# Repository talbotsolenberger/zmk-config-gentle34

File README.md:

This is a shield module for use with ZMK.

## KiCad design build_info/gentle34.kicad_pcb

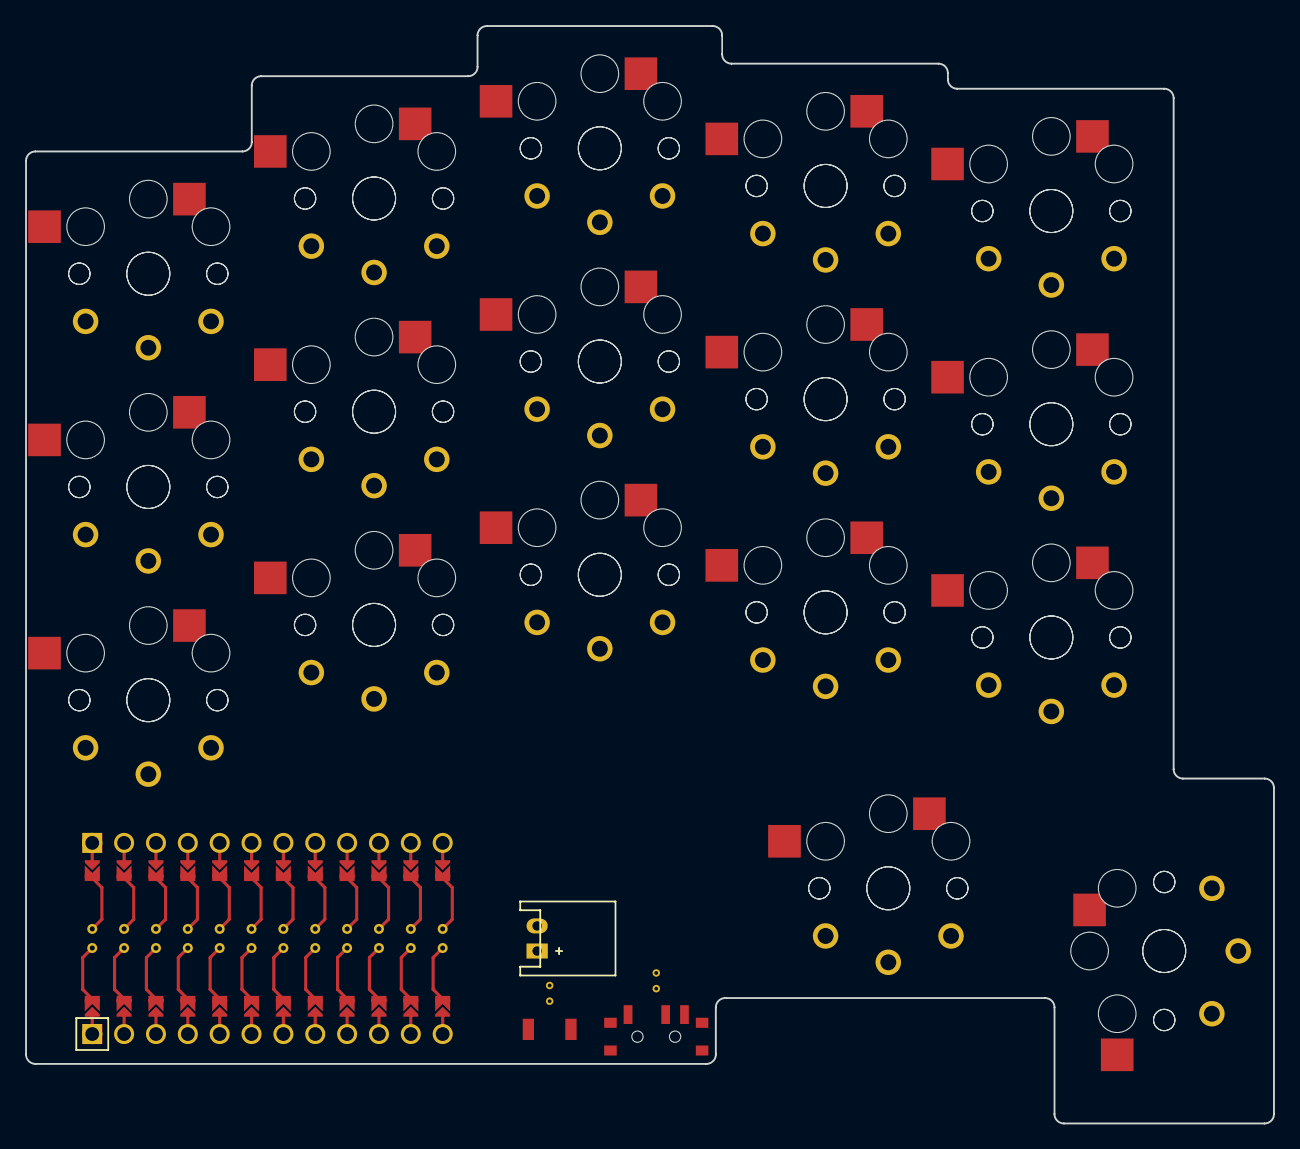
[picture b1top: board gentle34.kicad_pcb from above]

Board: 2 copper layers, 99.5 x 87.5 mm, 36 parts (0 on the bottom side), 18 nets, no tracks yet.

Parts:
JST1: JST_PH_S2B-PH-K_02x2.00mm_Angled
MCU1: ProMicro
S1, S2, S3, S4, S5, S6, S7, S8, S9, S10, S11, S12, S13, S14, S15, S16, S17, S18, S19, S20, S21, S22, S23, S24, S25, S26, S27, S28, S29, S30, S31, S32, S33, S34: PG1350

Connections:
GND: JST1.2, MCU1.2, MCU1.21, MCU1.22, S1.2, S2.2, S3.2, S4.2, S5.2, S6.2, S7.2, S8.2, S9.2, S10.2, S11.2, S12.2, S13.2, S14.2, S15.2, S16.2, S17.2, S18.2, S19.2, S20.2, S21.2, S22.2, S23.2, S24.2, S25.2, S26.2, S27.2, S28.2, S29.2, S30.2, S31.2, S32.2, S33.2, S34.2
P0: MCU1.23, S3.1, S4.1
P1: MCU1.24, S1.1, S2.1
P2: MCU1.20, S5.1, S6.1
P3: MCU1.19, S9.1, S10.1
P4: MCU1.18, S13.1, S14.1
P5: MCU1.17, S17.1, S18.1
P6: MCU1.16, S21.1, S22.1
P7: MCU1.15, S25.1, S26.1
P8: MCU1.14, S29.1, S30.1
P9: MCU1.13, S33.1, S34.1
P10: MCU1.12, S31.1, S32.1
P14: MCU1.10, S27.1, S28.1
P15: MCU1.9, S23.1, S24.1
P18: MCU1.8, S19.1, S20.1
P19: MCU1.7, S15.1, S16.1
P20: MCU1.6, S11.1, S12.1
P21: MCU1.5, S7.1, S8.1

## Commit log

2022-12-21 Initial User Config.
2022-12-21 initial user config
2022-12-21 Rename gentle34.conf.conf to gentle34.conf
2022-12-21 fixed build.yaml
2022-12-21 bug fixing kconfig.defconfig
2022-12-21 added keymap
2022-12-21 forgot to put anything in left overlay
2022-12-22 added gui to nav layer
2023-01-10 tweaked position of combos
2023-01-19 moved function keys to number layer. added arrow keys to left hand of nav layer.
2023-01-19 added enter to left hand nav layer
2023-01-19 added c to gaming layer on right hand
2023-01-20 added v to gaming layer right hand
2023-02-02 add ios discord macro
2023-02-04 typo
2023-12-14 isrt layout to alphas
2024-04-17 qwerty layout to alphas
2024-04-17 back to isrt layout to alphas
2024-04-25 nav left thumb into backspace
2024-05-27 Added gui to homerow pinkies for NixOS macros
2024-06-17 readded ralt to movement layer
2024-06-27 Added Unreal layer
2024-10-14 added LALT to homerow mods
2024-10-15 changed placement of LALT on base layer
2024-10-15 bug fix
2024-10-17 added discord mute button to nav layer
2024-11-16 added x to gaming layer
2024-11-16 added additional x to gaming layer for ease of use
2024-11-16 added z to right handed gaming layer
2024-11-18 added blutooth disconnect combo
2024-11-18 tweaked blutooth clear combo
2025-03-10 added second gaming layer
2025-03-17 troubleshooting media play/pause not working
2025-08-18 testing lock function on nav layer
2025-08-18 last lock keycode didn't work
2025-08-18 removed nonfunctional computer lock keycode
2025-11-18 Added alt+tab combo
2025-11-18 potential error with formatting
2025-11-18 missed two semicolons
2025-11-18 actually, missed another semi
2025-11-18 troubleshooting alt tab
2025-11-18 making the alt_tab transition smoother
2025-11-18 removed unused IOS stuff
2025-11-19 Updated to have all kicad files here too
2025-11-19 removed alt tab functionality. Have a better version working wiht autohotkey
2025-11-19 renamed folder to be less confusing
2025-11-28 Added Enter to home row with combos
2025-11-28 fixed missing ;
2025-11-28 missisigned keys to left hand Enter
2025-11-28 switched inputs for Enter combo and OS
    sys combo
2025-12-03 added CAPSLOCK to Nav layer to try to fix bug where keyboard goes full caps.
2025-12-14 Added ESC under Ctrl and Tab combos on base layer
2025-12-14 restructured files for updated ZMK
2025-12-14 nice_nano_v2 no longer supported? renamed to nice_nano and hoping it works?
2025-12-14 added zephyr/module.yaml
2025-12-14 updated west.yaml
2025-12-14 removed updated west.yaml.
2025-12-15 attempt to get this thing formatted right
2025-12-15 removed unnecessary configuration
2025-12-15 trying to fix github error
2025-12-15 west.yaml should point to the correct repository
2025-12-15 hold on it may have finally clicked
2025-12-15 West manifest was pointing to wrong branch
2025-12-15 changed build.yaml to just nice_nano
2025-12-15 Reconfigured repo to contain the shield module as well as the config
2025-12-15 changed west
2025-12-16 added reset firmware to build.yaml
2025-12-16 updated keymap to fix combo_tab and make comments more clear
2025-12-17 Changed bt_clr command to bt_clr_all. reorganized combos forc clarity
2025-12-17 Changed combo_tabs to less awkward button combos
2025-12-22 changed to switch back to v0.3
2026-01-01 Added DEL combo on right hand
2026-01-02 Shortened &mt time to hopefully make typing with symbols faster
2026-01-05 shortened hrl hold timing
2026-01-07 Removed caps_word macro and reformatted keymap
2026-01-07 renamed parts list'
2026-01-09 fixed incomplete keycode
2026-01-10 Added tab combo for gaming layer
2026-01-23 Update keymap for use with Aseprite
2026-01-23 Update keymap to make Aseprite combo for changing brush size easier.
2026-01-23 Update keymap for Aseprite Enter combo
2026-01-23 Update keymap so combo_del works on Aseprite layer as well. Move combo_ase_esc to a more comfortable location
2026-01-23 Update keymap to move &to Aseprite combo to one I can do with my right hand
2026-01-24 Move combo_ase_esc to a more comfortable position
2026-01-30 Add TAB to GAM2
2026-02-13 Add B binding to Game2 layer
2026-02-13 Remove LGUI from right pinky on Alpha layer for less errors when typing quickly
2026-02-13 Make combo section clearer to read with comments
2026-03-02 Move combos that change layers to the section of the layer they switch to
2026-04-07 Modify Aseprite layer to general Creative layer for use with blender on the left hand.
2026-04-07 Revert back to previous working version of boards
2026-04-07 Change version from v0.3 to main
